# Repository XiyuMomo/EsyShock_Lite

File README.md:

# EsyShock_Lite

> ## 简介
>
> 该项目旨在实现低成本的可编程电击设备，具有不低于60V 100mA的输出能力，同时板载单片机与usb转串口ic以实现用户自行烧写控制程序。
>
> * pcb相关文件使用kicad绘制

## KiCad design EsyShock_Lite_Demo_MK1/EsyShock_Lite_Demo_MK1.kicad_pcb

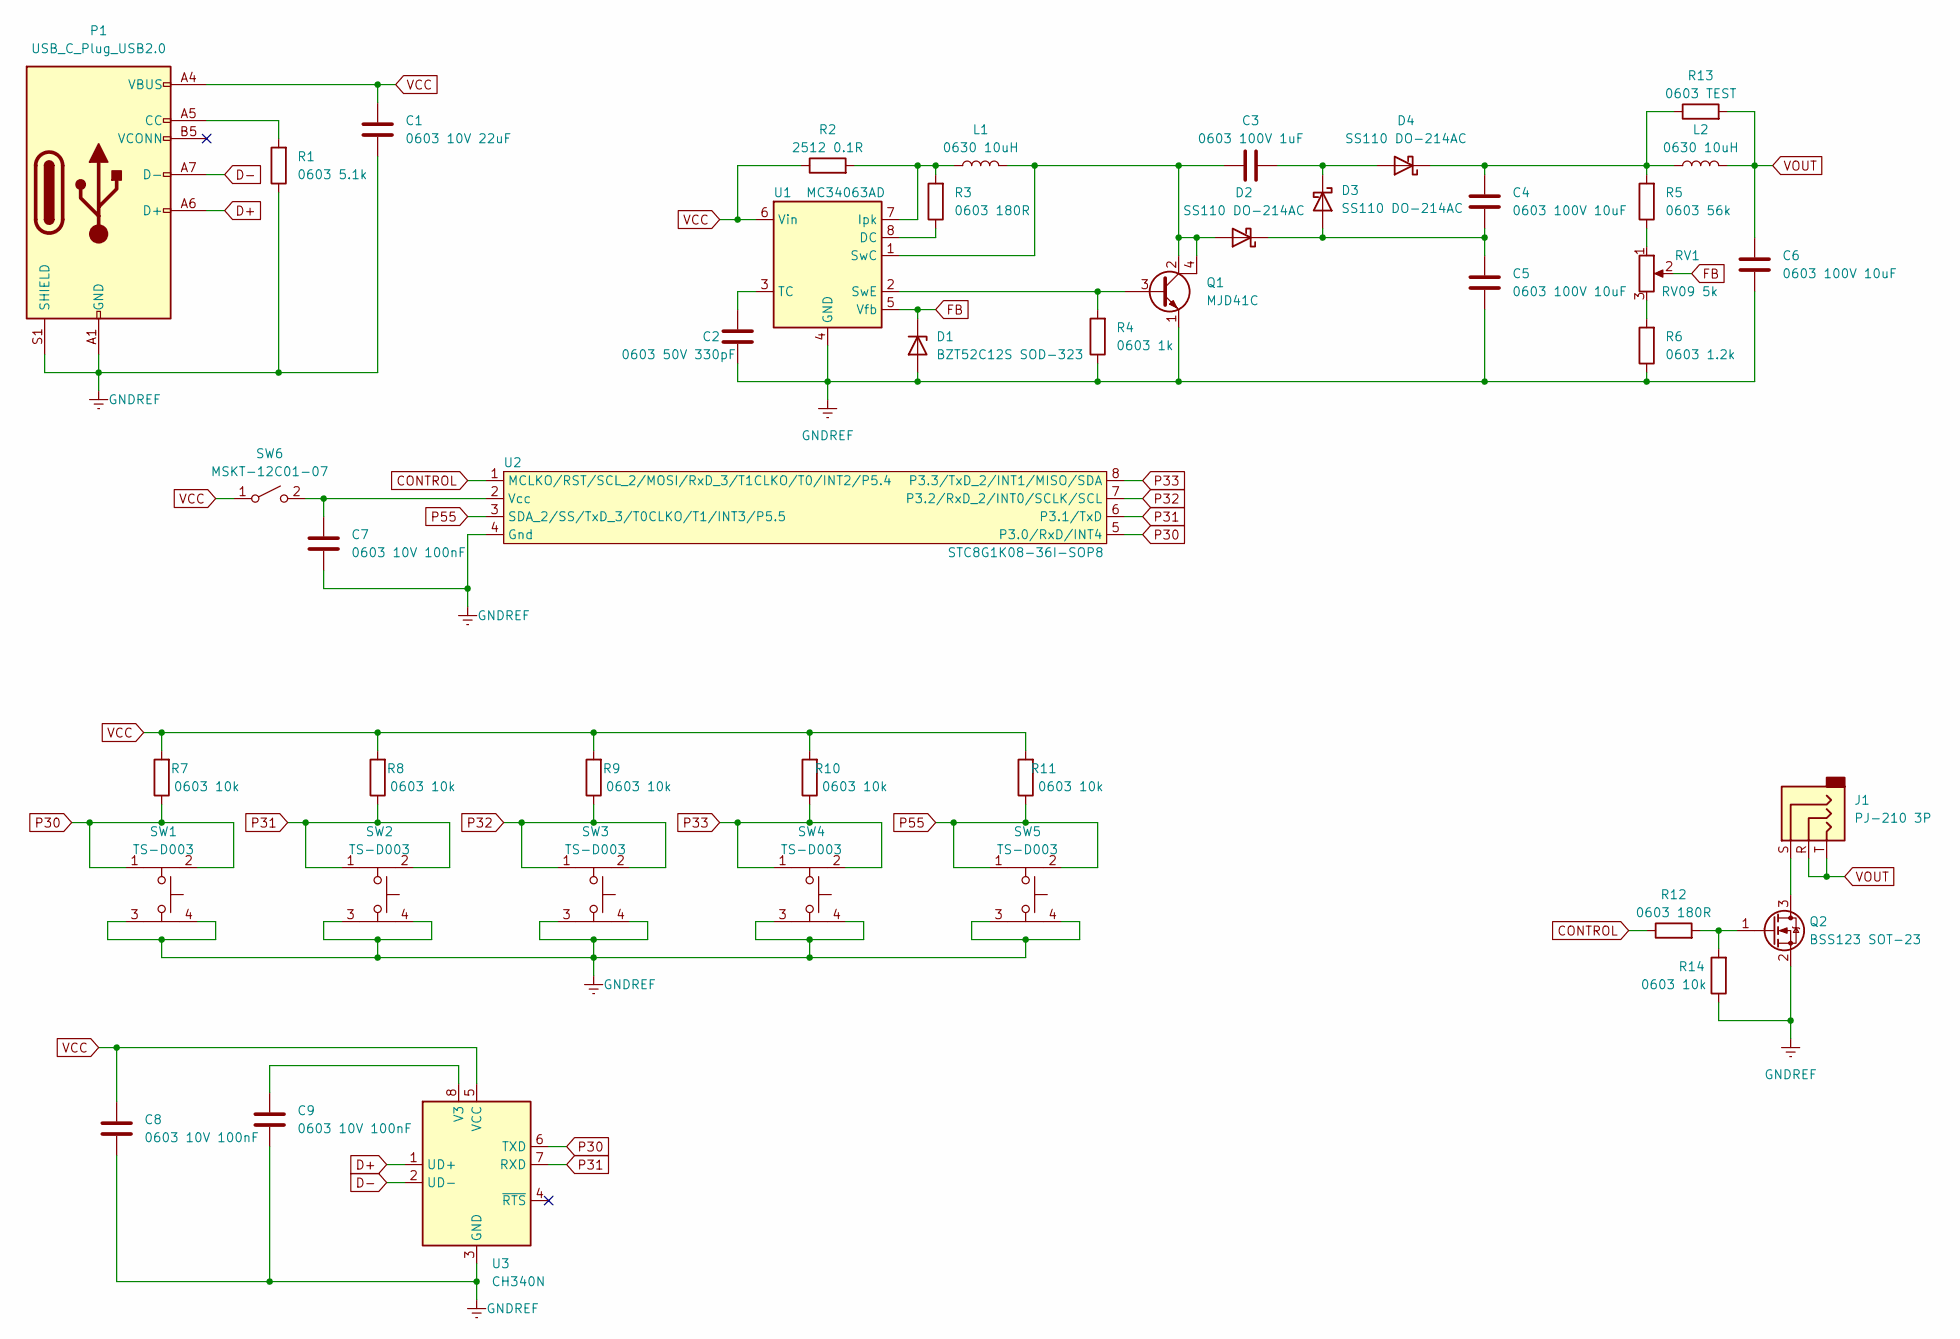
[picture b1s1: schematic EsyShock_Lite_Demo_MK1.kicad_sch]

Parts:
C1: 0603 10V 22uF; C_0603_1608Metric
C2: 0603 50V 330pF; C_0603_1608Metric
C3: 0603 100V 1uF; C_0603_1608Metric
C4, C5, C6: 0603 100V 10uF; C_0603_1608Metric
C7, C8, C9: 0603 10V 100nF; C_0603_1608Metric
D1: BZT52C12S SOD-323; D_SOD-323
D2, D3, D4: SS110 DO-214AC; D_SMA
J1: PJ-210 3P; Audio_Jack_PJ-210C_3P
L1, L2: 0630 10uH; Inductor_HC0630
P1: USB_C_Plug_USB2.0; USB_C_Receptacle_16P_01
Q1: MJD41C; TO-252-3_TabPin4
Q2: BSS123 SOT-23; SOT-23
R1: 0603 5.1k; R_0603_1608Metric
R2: 2512 0.1R; R_2512_6332Metric
R3, R12: 0603 180R; R_0603_1608Metric
R4: 0603 1k; R_0603_1608Metric
R5: 0603 56k; R_0603_1608Metric
R6: 0603 1.2k; R_0603_1608Metric
R7, R8, R9, R10, R11, R14: 0603 10k; R_0603_1608Metric
R13: 0603 TEST; R_0603_1608Metric
RV1: RV09 5k; Potentiometer_RV09_Vertical
SW1, SW2, SW3, SW4, SW5: TS-D003
SW6: MSKT-12C01-07
U1: MC34063AD; SOIC-8_3.9x4.9mm_P1.27mm
U2: STC8G1K08-36I-SOP8; SOP-8_3.9x4.9mm_P1.27mm
U3: CH340N; SOP-8_3.9x4.9mm_P1.27mm

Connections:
CONTROL: R12.1, U2.1 (MCLKO/RST/SCL_2/MOSI/RxD_3/T1CLKO/T0/IN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)
D+: P1.A6 (D+), P1.B6, U3.1 (UD+)
D-: P1.A7 (D-), P1.B7, U3.2 (UD-)
FB: D1.1 (K), RV1.2, U1.5 (Vfb)
GNDREF: C1.2, C2.2, C5.2, C6.2, C7.2, C8.2, C9.2, D1.2 (A), P1.A1 (GND), P1.A12 (GND), P1.B1 (GND), P1.B12 (GND), P1.S1 (SHIELD), Q1.1 (E), Q2.2 (S), R1.1, R4.1, R6.1, R14.1, SW1.3, SW1.4, SW2.3, SW2.4, SW3.3, SW3.4, SW4.3, SW4.4, SW5.3, SW5.4, U1.4 (GND), U2.4 (Gnd), U3.3 (GND)
unnamed: C2.1, U1.3 (TC)
unnamed: C3.1, D2.2 (A), L1.2, Q1.2 (C), Q1.4 (C), U1.1 (SwC)
unnamed: C3.2, D3.1 (K), D4.2 (A)
unnamed: C4.1, D4.1 (K), L2.1, R5.2, R13.1
unnamed: C4.2, C5.1, D2.1 (K), D3.2 (A)
unnamed: C7.1, SW6.2 (B), U2.2 (Vcc)
unnamed: C9.1, U3.8 (V3)
unnamed: L1.1, R2.2, R3.2, U1.7 (Ipk)
unnamed: P1.A5 (CC), R1.2
unnamed: Q1.3 (B), R4.2, U1.2 (SwE)
unnamed: Q2.1 (G), R12.2, R14.2
unnamed: J1.S, Q2.3 (D)
unnamed: R3.1, U1.8 (DC)
unnamed: R5.1, RV1.1
unnamed: R6.2, RV1.3
P30: R7.1, SW1.1, SW1.2, U2.5 (P3.0/RxD/INT4), U3.6 (TXD)
P31: R8.1, SW2.1, SW2.2, U2.6 (P3.1/TxD), U3.7 (RXD)
P32: R9.1, SW3.1, SW3.2, U2.7 (P3.2/RxD_2/INT0/SCLK/SCL)
P33: R10.1, SW4.1, SW4.2, U2.8 (P3.3/TxD_2/INT1/MISO/SDA)
P55: R11.1, SW5.1, SW5.2, U2.3 (SDA_2/SS/TxD_3/T0CLKO/T1/INT3/P5.5)
VCC: C1.1, C8.1, P1.A4 (VBUS), P1.A9 (VBUS), P1.B4 (VBUS), P1.B9 (VBUS), R2.1, R7.2, R8.2, R9.2, R10.2, R11.2, SW6.1 (A), U1.6 (Vin), U3.5 (VCC)
VOUT: C6.1, J1.R, J1.T, L2.2, R13.2

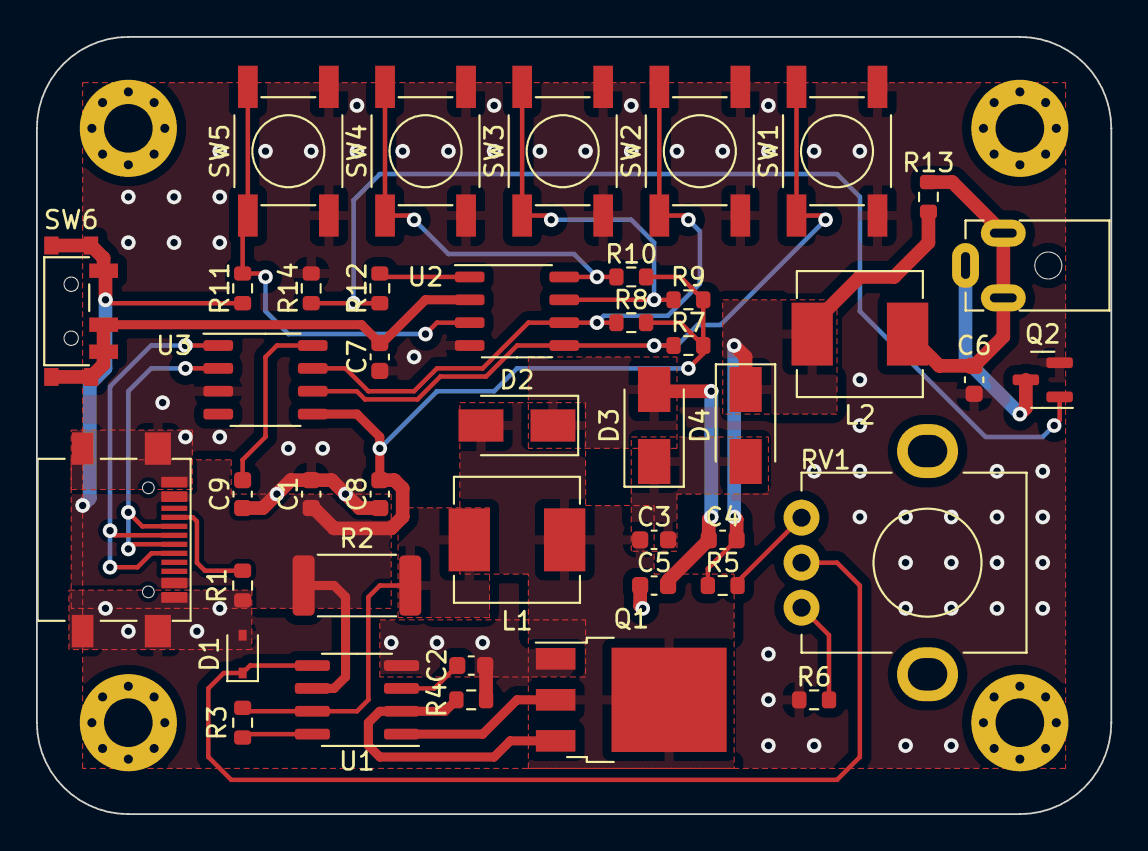
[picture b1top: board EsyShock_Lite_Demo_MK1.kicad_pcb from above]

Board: 2 copper layers, 59.7 x 43.2 mm, 43 parts (0 on the bottom side), 27 nets.
